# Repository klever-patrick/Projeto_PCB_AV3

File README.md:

Projeto Fabricação de PCB AV3

itens obrigatórios para o trabalho:
- lista de componentes com o orçamento dos mesmos;
- arquivos gerbers;
- pasta completa do projeto com o esquemático e o layout;
- Orçamento da fabricação da placa.

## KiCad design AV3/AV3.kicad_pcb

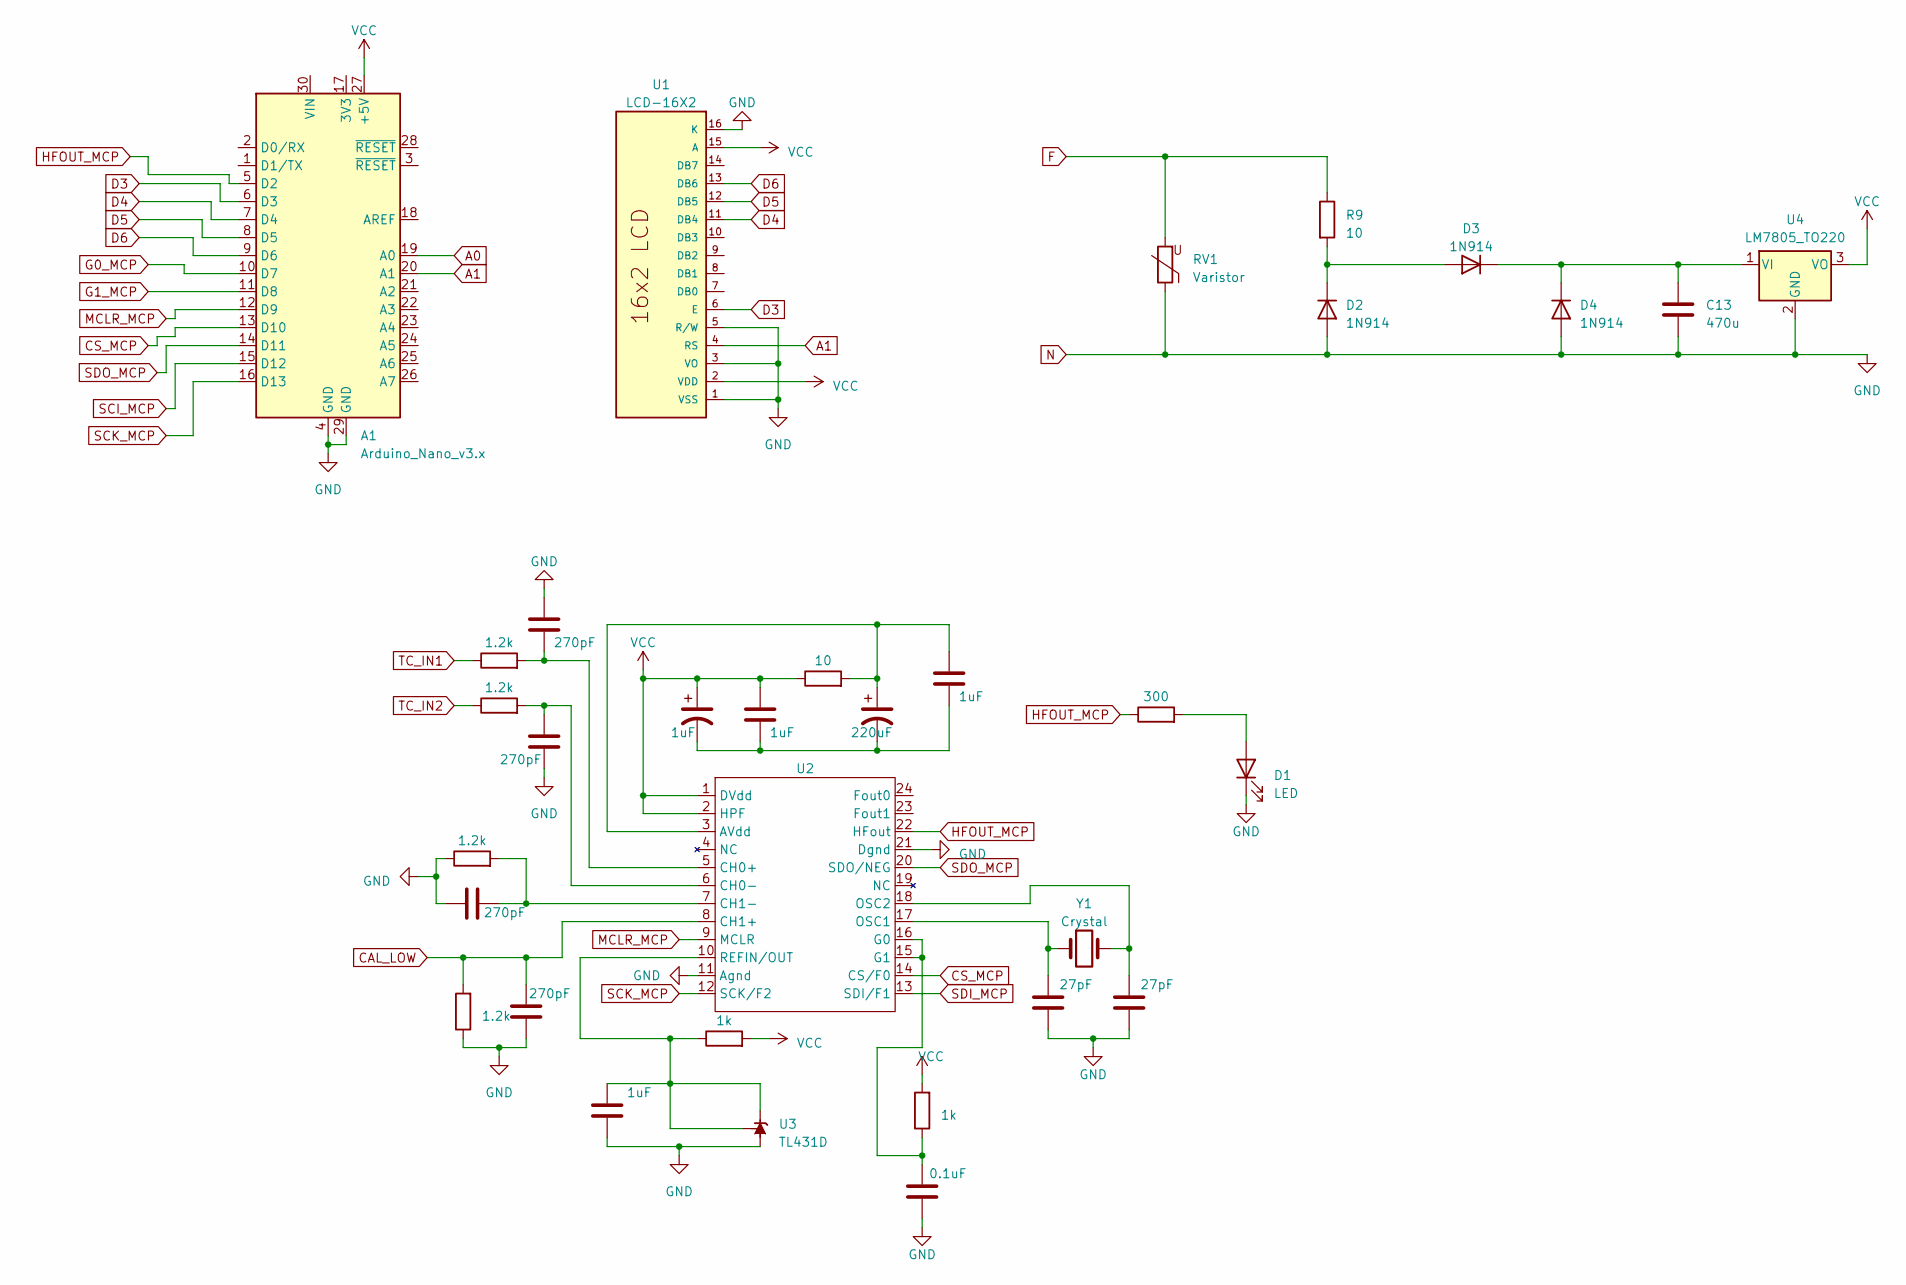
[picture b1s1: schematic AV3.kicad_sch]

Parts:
A1: Arduino_Nano_v3.x; Arduino_Nano
C1, C2, C4, C9: 1uF; CP_Radial_D10.0mm_P2.50mm
C3: 220uF; CP_Radial_D10.0mm_P2.50mm
C5, C6, C7, C8: 270pF; CP_Radial_D10.0mm_P2.50mm
C10: 0.1uF; CP_Radial_D10.0mm_P2.50mm
C11, C12: 27pF; CP_Radial_D10.0mm_P2.50mm
C13: 470u; CP_Radial_D10.0mm_P2.50mm
D1: LED; LED_D3.0mm
D2, D3, D4: 1N914; D_DO-35_SOD27_P7.62mm_Horizontal
R1, R9: 10; R_Axial_DIN0204_L3.6mm_D1.6mm_P2.54mm_Vertical
R2, R3, R4, R5: 1.2k; R_Axial_DIN0204_L3.6mm_D1.6mm_P2.54mm_Vertical
R6, R7: 1k; R_Axial_DIN0204_L3.6mm_D1.6mm_P2.54mm_Vertical
R8: 300; R_Axial_DIN0204_L3.6mm_D1.6mm_P2.54mm_Vertical
RV1: Varistor; RV_Disc_D7mm_W3.4mm_P5mm
U1: LCD-16X2; LCD-016N002L
U2: SOP65P780X200-24N
U3: TL431D; SOIC-8_3.9x4.9mm_P1.27mm
U4: LM7805_TO220; TO-220-3_Vertical
Y1: Crystal; Crystal_HC52-6mm_Vertical

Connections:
A0: A1.19 (A0)
A1: A1.20 (A1), U1.4 (RS)
CAL_LOW: C8.2, R5.2, U2.8 (CH1+)
CS_MCP: A1.13 (D10), U2.14 (CS/F0)
D3: A1.6 (D3), U1.6 (E)
D4: A1.7 (D4), U1.11 (DB4)
D5: A1.8 (D5), U1.12 (DB5)
D6: A1.9 (D6), U1.13 (DB6)
F: R9.1, RV1.2
G0_MCP: A1.10 (D7)
G1_MCP: A1.11 (D8)
HFOUT_MCP: A1.5 (D2), R8.1, U2.22 (HFout)
MCLR_MCP: A1.12 (D9), U2.9 (MCLR)
N: A1.4 (GND), A1.29 (GND), C5.1, C6.2, C7.1, C8.1, C9.1, C10.1, C11.1, C12.1, C13.2, D1.1 (K), D2.2 (A), D4.2 (A), R4.1, R5.1, RV1.1, U1.1 (VSS), U1.3 (VO), U1.5 (R/W), U1.16 (K), U2.11 (Agnd), U2.21 (Dgnd), U3.2 (A), U3.3 (A), U3.6 (A), U3.7 (A), U4.2 (GND)
unnamed: C1.2, C2.2, C3.2, C4.2
unnamed: D1.2 (A), R8.2
unnamed: D2.1 (K), D3.2 (A), R9.2
unnamed: C13.1, D3.1 (K), D4.1 (K), U4.1 (VI)
unnamed: C3.1, C4.1, R1.2, U2.3 (AVdd)
unnamed: C5.2, R2.2, U2.5 (CH0+)
unnamed: C6.1, R3.2, U2.6 (CH0-)
unnamed: C7.2, R4.2, U2.7 (CH1-)
unnamed: C10.2, R7.1, U2.15 (G1), U2.16 (G0)
unnamed: C11.2, U2.17 (OSC1), Y1.1
unnamed: C12.2, U2.18 (OSC2), Y1.2
unnamed: C9.2, R6.1, U2.10 (REFIN/OUT), U3.1 (K), U3.8 (REF)
SCI_MCP: A1.15 (D12)
SCK_MCP: A1.16 (D13), U2.12 (SCK/F2)
SDI_MCP: U2.13 (SDI/F1)
SDO_MCP: A1.14 (D11), U2.20 (SDO/NEG)
TC_IN1: R2.1
TC_IN2: R3.1
VCC: A1.27 (+5V), C1.1, C2.1, R1.1, R6.2, R7.2, U1.2 (VDD), U1.15 (A), U2.1 (DVdd), U2.2 (HPF), U4.3 (VO)

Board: 2 copper layers, 33 parts (0 on the bottom side), 26 nets, no tracks yet.

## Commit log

2023-04-25 Add README.md
2023-05-16 Add initial KiCAD files
2023-05-16 Add TCC pdf file
2023-05-23 Add arduino and LCD display
2023-05-25 Add power supply circuitry
2023-05-30 placa doida
2023-05-30 Add MCP3909
2023-05-30 footprint mcp3909
2023-05-30 listagem
